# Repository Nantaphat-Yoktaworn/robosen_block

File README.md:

# Robosen Tangible Coding Block System & RobosenJS SDK

> **Physical Tangible Modular Coding Block System & Multi-Platform SDK for the Robosen K1 Humanoid Robot**  
> Designed for Screenless STEM Learning for Young Children ($\le 7$ Years Old) and Advanced Robotics Developers.  
> **FCC ID:** `2ATNWK1` | **Live Verified Robot ID:** `K1-00457` (`3C:A5:51:94:97:70`) | **Firmware:** `VER:3.03L`

---

## 📑 Table of Contents

1. [Executive Overview & Educational Mission](#-executive-overview--educational-mission)
2. [System Architecture & Signal Flow](#-system-architecture--signal-flow)
3. [2-Phase Bi-Directional Bus Protocol (CRC-8)](#-2-phase-bi-directional-bus-protocol-crc-8)
4. [Python Native BLE Subsystem & Daemon](#-python-native-ble-subsystem--daemon)
5. [Hardware & Electrical Specifications](#-hardware--electrical-specifications)
6. [Project Documentation Sitemap](#-project-documentation-sitemap)
7. [Developer Guide & Upstream RobosenJS SDK](#-developer-guide--upstream-robosenjs-sdk)

---

## 🎯 Executive Overview & Educational Mission

### The Core Problem
Most modern coding curricula for children rely on tablets, smartphones, or computers (e.g., Scratch, Blockly). However, for **young children aged 7 and under** (Piaget’s Preoperational and early Concrete Operational stages), screens present significant developmental hurdles:
- **Abstract vs. Concrete Cognition:** Young children learn best through tactile, physical manipulation rather than abstract 2D screen coordinates.
- **Screen Fatigue & Distraction:** Excessive screen time causes disengagement, eye strain, and cognitive overload.
- **Disconnected Output:** Virtual sprites on screens lack the visceral spatial feedback and excitement of watching a physical bipedal robot walk, punch, balance, and cheer.

### The Tangible Coding Solution
This project creates a **tangible, screenless, modular physical block programming system**. Children configure solid coding blocks on the Master's **Config Dock**, then snap them together in a line to create an algorithmic sequence at the **Run Port**. When they press the big **Green "Start" Button** on the Master Block, the sequence compiles instantly, verifies checksums, commands the **Robosen K1 humanoid robot** via Bluetooth Low Energy (BLE), and lights up each physical block with a **bright pulsating green LED** in real time as the robot executes each step!

```text
┌──────────────────────────────────────────────────────────────────────────────────────────────────┐
│                                   PHYSICAL TANGIBLE CODING CHAIN                                 │
│                                                                                                  │
│   [ MASTER BLOCK ] ──► [ WALK BLOCK ] ──► [ TURN BLOCK ] ──► [ PUNCH BLOCK ] ──► [ END BLOCK ]   │
│   (Brain, Battery,     (Param: 3 steps)   (Param: 90° Right) (Action: Left Hook) (Terminator)    │
│    E-Ink Display,                                                                                │
│    2 Config Knobs,                                                                               │
│    Start Button)                                                                                 │
│          │                                                                                       │
│          ▼ (Bluetooth BLE 4.2 / 5.0 Stream)                                                      │
│   [ ROBOSEN K1 HUMANOID ROBOT ] ─── Executes commands step-by-step with real-time feedback!      │
└──────────────────────────────────────────────────────────────────────────────────────────────────┘
```

---

## ⚡ System Architecture & Signal Flow

### 1. Dual-Mode Hardware Bus & Port Architecture

### 2. Config Mode: Flash Programming & Data Flow

### 3. Run Mode: End-to-End Execution & Protocol Data Flow

The system operates across three interconnected layers:
1. **Physical Modular Block Bus (4-Pin Magnetic Interface):** Master Block (ESP32-S3 with E-Ink & Config Dock) $\longleftrightarrow$ Solid Smart Blocks (WCH CH32V003 RISC-V) $\longleftrightarrow$ Smart End Block.
2. **Master Embedded & Control Gateway:** Master ESP32-S3 coordinates discovery frames (`0xAA`), CRC-8 validation, step broadcasts (`0xBB`), and non-blocking BLE command dispatch.
3. **Hardware Gateway & Robot Layer (Python BLE Daemon & Robosen K1):** Persistent BLE connection to Robosen K1 with dynamic 100% action completion ACK resolution.

```mermaid
sequenceDiagram
    autonumber
    participant Master as Master Block (ESP32-S3)
    participant Docked as Action Block (At Config Dock)
    participant B1 as Smart Block 1 (Walk 3 Steps)
    participant B2 as Smart Block 2 (Punch Left)
    participant EndBlock as Smart End Terminator
    participant Robot as Robosen K1 Humanoid Robot

    Note over Master,Docked: CONFIGURATION MODE (At Master Config Dock)
    Master->>Docked: Send Write Config [0xCF, 0x02, ActionID, Param, CRC, 0x55]
    Note over Docked: Saves [ActionID, Param] to Internal Flash Memory
    Docked-->>Master: Send ACK [0xCF, 0x06, CRC, 0x55]
    Note over Master,Docked: Block LED Pulses Emerald Green (Saved!)

    Note over Master,EndBlock: PHASE 1: DISCOVERY & COMPILATION (Press Start Button)
    Master->>B1: Frame [0xAA, Len=0, Count=0, CRC] (Pin 3 TX)
    Note over B1: Sets Index=1, appends Flash Token 0x01 (Walk) + Param=3, Count=1
    B1->>B2: Frame [0xAA, Len=2, Count=1, 0x01, 0x03, CRC]
    Note over B2: Sets Index=2, appends Flash Token 0x10 (Punch) + Param=1, Count=2
    B2->>EndBlock: Frame [0xAA, Len=4, Count=2, 0x01, 0x03, 0x10, 0x01, CRC]
    EndBlock->>Master: Return Verified Program Frame over Pin 4 (Return RX Rail)
    Master->>Master: Validates CRC-8 Checksum & Queues Sequence

    Note over Master,Robot: PHASE 2: REAL-TIME EXECUTION & VISUAL STEP TRACKING
    Master-->>B1: Broadcast [0xBB, ActiveStep=1, TotalSteps=2, CRC] (Pin 4 RX_BUS)
    Note over B1: MyIndex(1) == ActiveStep(1) -> GLOWS BRIGHT PULSING GREEN!
    Master->>Robot: Send BLE Walk Command (Opcode 0x01)
    Robot->>Master: Locomotion completes -> Master sends Stop (0x0C)
    
    Master-->>B2: Broadcast [0xBB, ActiveStep=2, TotalSteps=2, CRC] (Pin 4 RX_BUS)
    Note over B1: Reverts to Mode Color (Blue)
    Note over B2: MyIndex(2) == ActiveStep(2) -> GLOWS BRIGHT PULSING GREEN!
    Master->>Robot: Send BLE Action "ProAction/Left Punch" (Opcode 0x17)
    Robot->>Master: Robot streams progress -> reaches 100% ACK (0x64)

    Note over Master,Robot: SEQUENCE EXECUTION COMPLETED
    Master->>Master: E-Ink Display: 'MISSION COMPLETE 🎉'
    Robot->>Robot: Stabilizes into Safe Stand Posture & Idles
```

---

## 📡 2-Phase Bi-Directional Bus Protocol (CRC-8)

To achieve native physical order auto-discovery, hot-plug resilience, and real-time visual feedback over a simple 4-pin magnetic connector, the system uses an **Enhanced 2-Phase Bi-Directional UART Protocol**:

### Standardized 4-Pin Pogo Connector Pinout
* **Pin 1 (`V+`):** Regulated 3.3V power rail supplied by Master Block.
* **Pin 2 (`GND`):** Common system ground.
* **Pin 3 (`UART TX_DOWN`):** Downstream point-to-point serial line (Master $\to$ Block 1 $\to$ Block 2 $\dots \to$ End).
* **Pin 4 (`UART RX_BUS`):** Continuous return rail & real-time step broadcast bus.

### Binary Frame Structures
All serial transmissions use binary frames protected by **CRC-8** (Polynomial: $x^8 + x^2 + x + 1$, `0x07`):

1. **Phase 1: Discovery & Compilation Frame (`Header = 0xAA`)**
   ```
   [ 0xAA ] [ PacketLen (N) ] [ BlockCount (K) ] [ Block 1 ID ] [ Param 1 ] ... [ CRC-8 ] [ 0x55 ]
   ```
2. **Phase 2: Live Step Broadcast Frame (`Header = 0xBB`)**
   ```
   [ 0xBB ] [ ActiveStep (1-N / 0xFF) ] [ TotalSteps (N) ] [ CRC-8 ] [ 0x55 ]
   ```

### Command Token Catalog & LED Color Mapping

| Token ID | Command Name | Parameter | Robosen BLE Mapping | LED Color |
| :---: | :--- | :--- | :--- | :---: |
| `0x01` | `MOVE_FORWARD` | Steps (`1`–`5`) | `0x01` (Walk Forward) | 🔵 Blue (`#1E88E5`) |
| `0x02` | `MOVE_BACKWARD`| Steps (`1`–`5`) | `0x05` (Walk Backward) | 🔵 Dark Blue (`#1565C0`) |
| `0x03` | `TURN_LEFT` | Angle (`45°`–`180°`) | `0x08` (Turn Left) | 🔷 Cyan (`#00ACC1`) |
| `0x04` | `TURN_RIGHT` | Angle (`45°`–`180°`) | `0x02` (Turn Right) | 🔷 Cyan (`#00ACC1`) |
| `0x07` | `MOVE_LEFT` | Side-steps (`1`–`5`)| `0x07` (Step Left) | 🟦 Sky Blue (`#039BE5`) |
| `0x08` | `MOVE_RIGHT` | Side-steps (`1`–`5`)| `0x03` (Step Right) | 🟦 Sky Blue (`#039BE5`) |
| `0x10` | `LEFT_PUNCH` | Reps (`1`–`3`) | `0x17` (`"ProAction/Left Punch"`) | 🔴 Red (`#E53935`) |
| `0x11` | `RIGHT_PUNCH`| Reps (`1`–`3`) | `0x17` (`"ProAction/Right Punch"`) | 🔴 Bright Red (`#D32F2F`) |
| `0x12` | `KUNG_FU` | Reps (`1`–`3`) | `0x17` (`"ProAction/Kung Fu"`) | 🟠 Orange (`#FB8C00`) |
| `0x13` | `BOOGALOO` | Reps (`1`–`3`) | `0x17` (`"Action/Boogaloo"`) | 🟣 Magenta (`#8E24AA`) |
| `0x14` | `PUSH_UPS` | Reps (`1`–`3`) | `0x17` (`"ProAction/Push Ups"`) | 🟤 Brown (`#6D4C41`) |
| `0x15` | `HANDSTAND` | Reps (`1`–`3`) | `0x17` (`"ProAction/Handstand"`) | 🟤 Brown (`#6D4C41`) |
| `0x16` | `SINGLE_KICK`| Reps (`1`–`3`) | `0x17` (`"ProAction/Left Kick"`) | 🔴 Red (`#E53935`) |
| `0x17` | `DO_SQUATS` | Reps (`1`–`3`) | `0x17` (`"ProAction/Do Squats"`) | 🟢 Green (`#43A047`) |
| `0x18` | `SAY_HELLO` | Reps (`1`–`3`) | `0x17` (`"ProAction/Say Hello"`) | 🩵 Teal (`#00897B`) |
| `0x19` | `CELEBRATE` | Reps (`1`–`3`) | `0x17` (`"ProAction/Celebrate"`) | 🟡 Yellow (`#FDD835`) |
| `0xEE` | `END_CAP` | Smart End Terminator | N/A (Return Rail Loopback) | 🟢 Soft Emerald Green (`#00E020`) |

---

## 🐍 Python Native BLE Subsystem & Daemon

To provide 100% reliable Bluetooth Low Energy communication on Windows 11/10 without requiring C++ MSVC compiler toolchains, the project includes a native Python BLE subsystem powered by `bleak` and Windows WinRT:

### 1. Persistent BLE Daemon ([`scripts/k1_ble_daemon.py`](scripts/k1_ble_daemon.py))
- **Persistent Long-Lived Connection:** Connects once on startup and keeps the BLE connection alive to eliminate reconnection latency.
- **Dynamic 100% Action Completion ACK:** Listens to BLE Characteristic `0xFFE1` notifications in real time. Actions resolve the exact millisecond the physical robot emits `action_progress: 100%` (`0x64`), allowing seamless back-to-back chaining without hardcoded delays.
- **Standing Posture Preservation (`move_head_only`):** Captures live standing angles of all 16 body/leg servos via `0xE9` (`jointSync`) so neck/head articulations rotate smoothly without snapping leg angles or causing balance loss.
- **Bidirectional JSON IPC:** Communicates over `stdin`/`stdout` with CLI tools and background processes.

### 2. Fast Command-Line Execution CLI ([`scripts/k1_action.py`](scripts/k1_action.py))
```powershell
# Query Live Telemetry & Battery
python scripts/k1_action.py status

# Locomotion Steps
python scripts/k1_action.py walk
python scripts/k1_action.py turn_left
python scripts/k1_action.py turn_right

# Martial Arts & Combat
python scripts/k1_action.py punch_left
python scripts/k1_action.py punch_right
python scripts/k1_action.py kung_fu
python scripts/k1_action.py single_kick

# Stunts, Acrobatics & Dances
python scripts/k1_action.py push_ups
python scripts/k1_action.py handstand
python scripts/k1_action.py boogaloo
python scripts/k1_action.py say_hello
python scripts/k1_action.py celebrate
python scripts/k1_action.py do_squats

# Head Servo Articulations & Posture
python scripts/k1_action.py default_stand
python scripts/k1_action.py head_left
python scripts/k1_action.py head_right
python scripts/k1_action.py head_center
python scripts/k1_action.py head_pan
```

### 3. Interactive Joint Kinematics Controller ([`scripts/k1_joint_controller.py`](scripts/k1_joint_controller.py))
Interactive keyboard controller for all 17 digital servos with real-time safeguard limit enforcement, visual gauges, and error handling:
```powershell
python scripts/k1_joint_controller.py
```
- **Connection:** `C` (Connect/Reconnect) / `D` (Disconnect cleanly)
- **Select Joint:** `↑` / `↓` or `[` / `]` or Number `0`–`9`
- **Adjust Value:** `←` / `→` (or `PageDown` / `PageUp` for ±10)
- **Step Size:** `+` / `-` (1, 2, 5, 10)
- **Reset:** `R` (active joint) / `Shift+R` (all 17 stand pose)
- **Torque:** `U` (free joints for manual posing) / `L` (lock holding torque)

### 4. Interactive Telemetry & Control Suite ([`scripts/k1_ble_tester.py`](scripts/k1_ble_tester.py))
```powershell
python scripts/k1_ble_tester.py
```

---

## 🛠️ Hardware & Electrical Specifications

Complete hardware specifications are detailed in [`docs/specs/PHYSICAL_BLOCK_SYSTEM_SPEC.md`](file:///Users/nnnn/Projects/robosen_block/docs/specs/PHYSICAL_BLOCK_SYSTEM_SPEC.md), [`docs/specs/PROTOTYPE_00_SPEC.md`](file:///Users/nnnn/Projects/robosen_block/docs/specs/PROTOTYPE_00_SPEC.md) (Breadboard Proof-of-Concept), and [`docs/specs/PROTOTYPE_01_SPEC.md`](file:///Users/nnnn/Projects/robosen_block/docs/specs/PROTOTYPE_01_SPEC.md) (First Custom PCB Version):

### 1. Master Controller Breadboard Wiring & Pinout (Prototype #0)

```text
  (+) Red Rail  (+3.3V) ◄═════════[ 🔴 RED ]════════ ESP32 3V3 Pin
  (-) Blue Rail (GND)   ◄═════════[ ⚫ BLACK ]══════ ESP32 GND Pin

  [ KNOB 1: KY-040 Action Selector ]
   • VCC / +  ──► [ 🔴 RED ]    ──► (+) 3.3V Power Rail
   • GND      ──► [ ⚫ BLACK ]  ──► (-) Ground Rail
   • CLK      ──► [ 🟡 YELLOW ] ──► ESP32 GPIO 8
   • DT       ──► [ 🟢 GREEN ]  ──► ESP32 GPIO 9
   • SW       ──► [ 🔵 BLUE ]   ──► ESP32 GPIO 10

  [ KNOB 2: KY-040 Parameter Adjuster ]
   • VCC / +  ──► [ 🔴 RED ]    ──► (+) 3.3V Power Rail
   • GND      ──► [ ⚫ BLACK ]  ──► (-) Ground Rail
   • CLK      ──► [ ⚪ WHITE ]  ──► ESP32 GPIO 11 (CW = Increase)
   • DT       ──► [ 🟤 BROWN ]  ──► ESP32 GPIO 12
   • SW       ──► [ 🔘 GRAY ]   ──► ESP32 GPIO 13

  [ Tactile Start / Confirm Button - Green (4-Pin DIP, SW3) ]
   • Top-Right Pin ──► [ 🟠 ORANGE ] ──► ESP32 GPIO 14 (Internal Pull-Up)
   • Bottom-Left   ──► [ ⚫ BLACK ]  ──► (-) Ground Rail (Diagonal GND Return)

  [ Tactile Cancel / Stop Button - Red (4-Pin DIP, SW5) ]
   • Top-Right Pin ──► [ 🔴 RED/ORANGE ] ──► ESP32 GPIO 2 (Internal Pull-Up)
   • Bottom-Left   ──► [ ⚫ BLACK ]       ──► (-) Ground Rail (Diagonal GND Return)

  [ Battery Voltage Monitoring Divider (ADC1_CH0) ]
   • Divider Top   ──► VBAT_SW (Switched Battery Voltage Rail)
   • Midpoint (Sense)──► ESP32 GPIO 1 (BATSENSE) with 100nF Ceramic Filter Cap to GND
   • Divider Bottom──► (-) Ground Rail
```

| Component / Function | ESP32-S3 GPIO | Wire Color | Role / Description | Status |
| :--- | :---: | :---: | :--- | :---: |
| **+3.3V Power Rail** | `3V3` | 🔴 **Red** | Unified 3.3V DC Power Bus | ✅ Verified |
| **GND Common Rail** | `GND` | ⚫ **Black** | Common Ground Bus | ✅ Verified |
| **Battery Sense (ADC)** | `GPIO 1` | — | ADC1_CH0 1:1 Divider (100k/100k + 100nF) | ✅ Hardware Implemented |
| **Stop / Cancel Button**| `GPIO 2` | 🔴 **Red** | Red Tactile Button (`SW5`): Emergency Stop / Cancel / Back | ✅ Hardware Implemented |
| **Start / Run Button** | `GPIO 14` | 🟢/🟠 **Green/Orange**| Green Tactile Button (`SW3`): Confirm / Start / Next | ✅ Verified |
| **Knob 1 CLK** | `GPIO 8` | 🟡 **Yellow** | Action Selection Direction A | ✅ Verified |
| **Knob 1 DT** | `GPIO 9` | 🟢 **Green** | Action Selection Direction B | ✅ Verified |
| **Knob 1 SW** | `GPIO 10` | 🔵 **Blue** | Action Select Confirmation | ✅ Verified |
| **Knob 2 CLK** | `GPIO 11` | ⚪ **White** | Parameter Adjust Clock (CW = +) | ✅ Verified |
| **Knob 2 DT** | `GPIO 12` | 🟤 **Brown** | Parameter Adjust Data | ✅ Verified |
| **Knob 2 SW** | `GPIO 13` | 🔘 **Gray** | Parameter Reset / BLE Save | ✅ Verified |
| **Onboard Status RGB** | `GPIO 48` | *Internal* | 🟢 Ready \| 🔵 Scan \| 🟡 TX | ✅ Verified |
| **Config Dock UART** | `GPIO 17, 18` | 🔘 Gray / 🟣 Purple | Write Action (`0xCF`) & Read ACK | ✅ Verified |
| **Run Chain Bus UART**| `GPIO 15, 16` | 🟢 Green / ⚪ White | Phase 1 Discovery (`0xAA`) & Run (`0xBB`)| ✅ Verified |
| **E-Ink Display (SPI)** | `GPIO 4,5,6,7,21,38`| — | 2.13" DEPG0213BN SSD1680 (746ms Partial, Zero-Flicker Boot) | ✅ Verified |

### 2. Block Hardware Specifications
- **Master Block MCU:** ESP32-S3 (Dual-Core Xtensa LX7, Native Bluetooth BLE 5.0, SPI for E-Ink, and Dual UARTs for Config Dock & Run Chain).
- **Master UI & Display:** 2.13" E-Ink E-Paper display (DEPG0213BN / SSD1680, $71 \times 30\text{ mm}$ outline) + Dual Rotary Dials (Action & Parameter) + Dual Tactile Buttons (Green Start/Confirm & Red Stop/Cancel) + Battery Sense Monitor.
- **Visual Feedback (No Buzzer):** Master & Block WS2812B RGB LEDs with rich light choreography (emerald green flash ACK, data comet compilation wave, live step glowing green, rainbow victory sparkle).
- **Solid Modular Block MCUs (Unified Slave PCB):** Ultra-low-cost WCH CH32V003 (32-bit RISC-V, ~$0.15) with internal non-volatile flash parameter storage. **Action Blocks and Smart End Blocks share the exact same physical carrier PCB** ([`hardware/action_block/`](file:///Users/nnnn/Projects/robosen_block/hardware/action_block/)); End Block mode (`0xEE`) is configured via firmware on MCU Pin 15 (`PD0`), eliminating separate PCB fabrication or manual jumpers. Zero potentiometers or buttons on individual blocks!
- **Power & Charging:** Single 18650 3.7V Li-ion cell with onboard TP4056 USB-C charging, BMS protection, and TPS63020 3.3V synchronous buck-boost regulator.
- **Physical Connector:** Standardized 4-pin polarized magnetic pogo connector with reverse-polarity protection and RC debouncing filters.

### 3. Firmware Deliverables & Hardware Verification

| Module | Hardware Target | Source Location | Description | Status |
| :--- | :--- | :--- | :--- | :---: |
| **Master Controller** | ESP32-S3 | [`firmware/esp32_master/`](file:///Users/nnnn/Projects/robosen_block/firmware/esp32_master/) | BLE Central, NVS pairing, Dual-Knob UI, Dual Buttons (Green GPIO 14, Red GPIO 2), Battery ADC (GPIO 1), Run Chain Engine (`0xAA`/`0xBB`) | ✅ **Production Verified** |
| **Action Block Firmware** | WCH CH32V003 | [`firmware/ch32v003_action_block/`](file:///Users/nnnn/Projects/robosen_block/firmware/ch32v003_action_block/) | Unified C RISC-V firmware (2-Phase Binary V2, Config Dock, WS2812B) | ✅ **Flashed on Silicon** |
| **Smart End Block Firmware** | WCH CH32V003 | [`firmware/ch32v003_end_block/`](file:///Users/nnnn/Projects/robosen_block/firmware/ch32v003_end_block/) | Active loopback line driver, CRC-8 validation, rainbow sparkle (`0xEE`) | ✅ **Flashed on Silicon** |
| **Master Soldering Test** | ESP32-S3 | [`firmware/tests/master_soldering_test/`](file:///Users/nnnn/Projects/robosen_block/firmware/tests/master_soldering_test/) | All-input hardware verification suite (encoders, dual buttons, battery sense, e-paper, RGB) | ✅ **Hardware Verified** |
| **Standalone E-Ink Test** | ESP32-S3 | [`firmware/tests/standalone_eink_test/`](file:///Users/nnnn/Projects/robosen_block/firmware/tests/standalone_eink_test/) | 2.13" E-Paper DEPG0213BN driver benchmark, zero-flicker boot, partial refresh (1.34 Hz) | ✅ **Verified** |
| **ESP32 SWIO Programmer** | ESP32 / ESP32-S3 | [`firmware/tools_programmer/esp32_ch32v003_programmer/`](file:///Users/nnnn/Projects/robosen_block/firmware/tools_programmer/esp32_ch32v003_programmer/) | High-speed 1-wire SWIO debugger & chunked Python flasher (`flash_tool.py`) | ✅ **Utility** |
| **Arduino Uno Programmer** | Arduino Uno R3 | [`firmware/tools_programmer/arduino_uno_ch32v003_programmer/`](file:///Users/nnnn/Projects/robosen_block/firmware/tools_programmer/arduino_uno_ch32v003_programmer/) | Ardulink 16MHz assembly bit-banging flasher for `minichlink` | ✅ **Utility** |
| **Master Carrier PCB** | KiCad 10.0.6 | [`hardware/master_block/`](file:///Users/nnnn/Projects/robosen_block/hardware/master_block/) | Custom carrier motherboard PCB project (25.40mm row spacing, 100% routed, 0 DRC violations) | ✅ **Active Production Design** |
| **Modular Slave PCB (Action & End)** | KiCad 10.0.6 | [`hardware/action_block/`](file:///Users/nnnn/Projects/robosen_block/hardware/action_block/) | Unified 32×32mm carrier PCB for both Action Blocks and Smart End Blocks (Pin 15 / `PD0` configurable), centered pogo docks, 3-pin RGB header, 0 DRC violations | ✅ **Ordered & Verified** |

---

## 📚 Project Documentation Sitemap

| Document | Description |
| :--- | :--- |
| [`PROJECT_SUMMARY.md`](file:///Users/nnnn/Projects/robosen_block/PROJECT_SUMMARY.md) | Comprehensive executive project summary, mission, and comparison matrix |
| [`MEMORY.md`](file:///Users/nnnn/Projects/robosen_block/MEMORY.md) | Master technical knowledge base, verified hardware diagnostics, and opcode catalog |
| [`docs/specs/PHYSICAL_BLOCK_SYSTEM_SPEC.md`](file:///Users/nnnn/Projects/robosen_block/docs/specs/PHYSICAL_BLOCK_SYSTEM_SPEC.md) | Hardware, electrical, connector pinout, and 2-phase protocol specifications |
| [`docs/specs/PROTOTYPE_00_SPEC.md`](file:///Users/nnnn/Projects/robosen_block/docs/specs/PROTOTYPE_00_SPEC.md) | Prototype #0: Breadboard proof-of-concept engineering specification, wiring & test guides |
| [`docs/specs/PROTOTYPE_01_SPEC.md`](file:///Users/nnnn/Projects/robosen_block/docs/specs/PROTOTYPE_01_SPEC.md) | Prototype #1: First custom PCB release engineering specification, JLCPCB orders & assembly |
| [`docs/specs/PROTOTYPE_01_1_SPEC.md`](file:///Users/nnnn/Projects/robosen_block/docs/specs/PROTOTYPE_01_1_SPEC.md) | Prototype #1-1: Master Block PCB respin specification (ESP32-S3 25.40mm socket correction) |
| [`docs/specs/IMPROVEMENT_PLAN.md`](file:///Users/nnnn/Projects/robosen_block/docs/specs/IMPROVEMENT_PLAN.md) | 5-Pillar Master Improvement Plan and future production roadmap |
| [`docs/specs/ROBOSEN_K1_DOCUMENTATION.md`](file:///Users/nnnn/Projects/robosen_block/docs/specs/ROBOSEN_K1_DOCUMENTATION.md) | Official Robosen K1 reference manual, kinematics, voice commands, and safety guide |
| [`docs/master_block_wiring.html`](file:///Users/nnnn/Projects/robosen_block/docs/master_block_wiring.html) | Interactive Master Block BOM, color-coded pinout wiring table, and battery circuit guide |
| [`docs/mounting_and_enclosure_spec.md`](file:///Users/nnnn/Projects/robosen_block/docs/mounting_and_enclosure_spec.md) | Enclosure, M3 standoff boss clearances, and 3D casing specifications |
| [`docs/K1_HARDWARE_AUDIT_REPORT.md`](file:///Users/nnnn/Projects/robosen_block/docs/K1_HARDWARE_AUDIT_REPORT.md) | Live physical robot hardware diagnostics, telemetry verification, and action catalog dump |
| [`docs/plans/robosen_14_weeks_plan.md`](file:///Users/nnnn/Projects/robosen_block/docs/plans/robosen_14_weeks_plan.md) | 14-Week project operational timeline, task breakdown, and milestone tracking |
| [`docs/plans/TIMELINE_INFOGRAPHIC.md`](file:///Users/nnnn/Projects/robosen_block/docs/plans/TIMELINE_INFOGRAPHIC.md) | Timeline visual concept, ASCII art chart, and Canva design data |
| [`docs/assignments/RESEARCH_SUMMARY.md`](file:///Users/nnnn/Projects/robosen_block/docs/assignments/RESEARCH_SUMMARY.md) | Academic coursework research review summary (AS01) |
| [`hardware/master_block/`](file:///Users/nnnn/Projects/robosen_block/hardware/master_block/) | KiCad 10 Master Block PCB project (Corrected 25.40mm socket spacing, 100% routed) |
| [`hardware/action_block/`](file:///Users/nnnn/Projects/robosen_block/hardware/action_block/) | KiCad 10 Action Block PCB project, routing report, and production Gerbers |
| [`archive/prototype_1_0_retired/`](file:///Users/nnnn/Projects/robosen_block/archive/prototype_1_0_retired/) | Retired Prototype #1 files (preserved for historical defect audit) |

---

## 💻 Developer Guide & Upstream RobosenJS SDK

### Getting Started (Node.js SDK)
- Requires [Node.js](https://nodejs.org/en/download) (v22+)
- Install dependencies: `npm install`
- Run linting: `npm run lint`

### Programming API (JavaScript / TypeScript)
```js
import { K1 } from "robosen-js";

const k1 = new K1();
await k1.on();
await k1.volume(100);
await k1.autoStand(false);
await k1.moveForward();
await k1.leftPunch();
await k1.headLeft();
await k1.leftHand("+40%", 30);
await k1.audio("AppSysMS/101");
await k1.wait(3000);
await k1.end();
```

### CLI Utilities
```powershell
# Interactive REPL
npm run k1:repl

# Gamepad / Keyboard Controller
npm run k1:control

# Natural Language LLM Prompt (Requires OPENAI_API_KEY)
npm run k1:prompt
```

---

## 📄 License & Attribution

This project is licensed under the **[Apache License 2.0](LICENSE)**.

- **Original Base Library:** Core reverse-engineered protocol parser derived from [RobosenJS](https://github.com/oklemenz/RobosenJS) by Oliver Klemenz (Apache-2.0 License).
- **Physical Modular Tangible Coding Blocks:** Hardware specifications (CH32V003 bus, TP4056 power management) and 2-phase binary protocol with CRC-8 developed by [Nantaphat Yoktaworn](https://github.com/Nantaphat-Yoktaworn).
- **Python Subsystem:** Native background BLE daemon, IPC bridge, and interactive joint safeguard controller developed by [Nantaphat Yoktaworn](https://github.com/Nantaphat-Yoktaworn).
- **Trademarks:** Robosen is a registered trademark of Robosen Robotics. This open-source project is independently developed and not officially affiliated with or endorsed by Robosen.

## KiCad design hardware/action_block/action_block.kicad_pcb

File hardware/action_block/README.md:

# Robosen Tangible Action Block Hardware & PCB Design

> **Project:** Tangible Modular Coding Block System for Robosen Robot  
> **Target Module:** Modular Action Block (CH32V003 RISC-V Slave)  
> **Form Factor:** 32.0 mm × 32.0 mm 2-Layer FR-4 Carrier PCB (1.6 mm thickness, 1 oz copper)  
> **KiCad Version:** KiCad 10.0.6  
> **Fabrication Status:** **ORDERED AT JLCPCB (October 5, 2026)** — `robosen_action_block_gerbers.zip`  

---

## 1. System Overview & Electrical Architecture

Every Action Block is a drop-proof, solid modular unit with **zero moving parts** (no potentiometers, dials, or buttons). It contains:
1. **Microcontroller (`MCU`)**: **TENSTAR CH32V003F4P6** 2×11 DIP module (WCH 32-bit RISC-V core @ 24 MHz, 16 KB Flash, 2 KB SRAM).
2. **Visual Feedback (`RGB`)**: 3-pin 2.54 mm pitch header for a pre-soldered **WS2812 RGB LED module** (Top-to-Bottom: `GND`, `VCC`, `IN`).
3. **Decoupling Capacitor (`C104`)**: 100 nF ceramic capacitor placed adjacent to `VDD` and `GND`.
4. **Upstream Pogo Connector (`IN`)**: 4-pin 2.54 mm pitch magnetic pogo interface, **vertically centered** at $Y = 72.50\text{ mm}$.
5. **Downstream Pogo Connector (`OUT`)**: 4-pin 2.54 mm pitch magnetic pogo interface, **vertically centered** at $Y = 72.50\text{ mm}$ (ensures collinear flush alignment across chained blocks).
6. **Programming Header (`PROG`)**: 3-pin 2.54 mm header (`GND`, `3V3`, `SWIO`) for rapid 1-wire firmware flashing via `minichlink` or ESP32 programmer.

---

## 2. Pinout & Net Assignments

### 4-Pin Pogo Interface (`IN` & `OUT`, Centered at $Y = 72.50\text{ mm}$)

| Pin # | Signal Name | Upstream Connector (`IN`) | Downstream Connector (`OUT`) |
|:---:|:---|:---|:---|
| **1** | `+3V3` | Power Input ($Y = 68.69\text{ mm}$) | Power Output ($Y = 68.69\text{ mm}$) |
| **2** | `GND` | System Ground Reference ($Y = 71.23\text{ mm}$) | System Ground Reference ($Y = 71.23\text{ mm}$) |
| **3** | `UART_DATA` | Point-to-Point Input (`/RX_IN` $\to$ `PD6`, $Y = 73.77\text{ mm}$) | Point-to-Point Output (`/TX_OUT` $\gets$ `PD5`, $Y = 73.77\text{ mm}$) |
| **4** | `RETURN_BUS`| Continuous Return Rail Pass-Through ($Y = 76.31\text{ mm}$) | Continuous Return Rail Pass-Through ($Y = 76.31\text{ mm}$) |

> **Return Rail Detour:**  
> The `/RETURN_BUS` rail is routed on `B.Cu` ($0.40\text{ mm}$) with a 45° detour below the MCU DIP socket at $Y = 87.25\text{ mm}$ to prevent shorting through-hole pins 4 & 15.

### WS2812 RGB LED Header (`RGB`, 1×03 Pin Header)

| Pin # | Silk Label | Board Position ($X, Y$) | Net Assignment | Notes |
|:---:|:---|:---|:---|:---|
| **1** | `GND` | $(84.00, 59.96)\text{ mm}$ (Top) | `GND` | Thermal relief connection to continuous GND planes |
| **2** | `VCC` | $(84.00, 62.50)\text{ mm}$ (Middle) | `+3V3` | $0.60\text{ mm}$ power bus connection |
| **3** | `IN` | $(84.00, 65.04)\text{ mm}$ (Bottom) | `/LED_DIN` | High-speed 800 kHz signal to MCU pin 6 (`PA2`) |

### Programming & Debug Header (`PROG`, 1×03 Pin Header)

| Pin # | Silk Label | Board Position ($X, Y$) | Net Assignment |
|:---:|:---|:---|:---|
| **1** | `GND` | $(109.50, 81.42)\text{ mm}$ | `GND` |
| **2** | `3V3` | $(109.50, 83.96)\text{ mm}$ | `+3V3` |
| **3** | `SWIO` | $(109.50, 86.50)\text{ mm}$ | `/SWIO` (`PD1` on MCU pin 16) |

---

## 3. PCB Layout & Manufacturing Specifications

| Parameter | Specification |
| :--- | :--- |
| **Dimensions** | $32.00\text{ mm} \times 32.00\text{ mm}$ |
| **Layers** | 2 Layers (`F.Cu`, `B.Cu`) |
| **Thickness** | $1.6\text{ mm}$ FR-4 |
| **Copper Weight** | 1 oz ($35\text{ }\mu\text{m}$) |
| **Surface Finish** | Lead-Free HASL (or ENIG) |
| **Min Track / Spacing**| $0.30\text{ mm} / 0.25\text{ mm}$ ($0.60\text{ mm}$ for `+3V3`, $0.40\text{ mm}$ for `/RETURN_BUS`) |
| **Min Drill Size** | $0.85\text{ mm}$ (Zero vias; all connections use through-hole component pads) |
| **Ground Planes** | Continuous filled copper zones on both `F.Cu` and `B.Cu` with thermal reliefs |

---

## 4. Verification & Dual-Agent Audit

* **KiCad DRC**: **0 Errors, 0 Unconnected Items, 0 Copper Clearance Violations**.
* **Dual-Agent Verification**: Independently audited and verified by Antigravity and Codex Astra (`gpt-6-astra`).
* **Artifacts**:
  * Gerber Package: [`robosen_action_block_gerbers.zip`](robosen_action_block_gerbers.zip)
  * Schematic PDF: [`action_block_schematic.pdf`](action_block_schematic.pdf)
  * Top 3D Render: [`pcb_preview/action_block_top.png`](pcb_preview/action_block_top.png)
  * Bottom 3D Render: [`pcb_preview/action_block_bottom.png`](pcb_preview/action_block_bottom.png)
  * Routed Vector: [`pcb_preview/action_block_routed.svg`](pcb_preview/action_block_routed.svg)

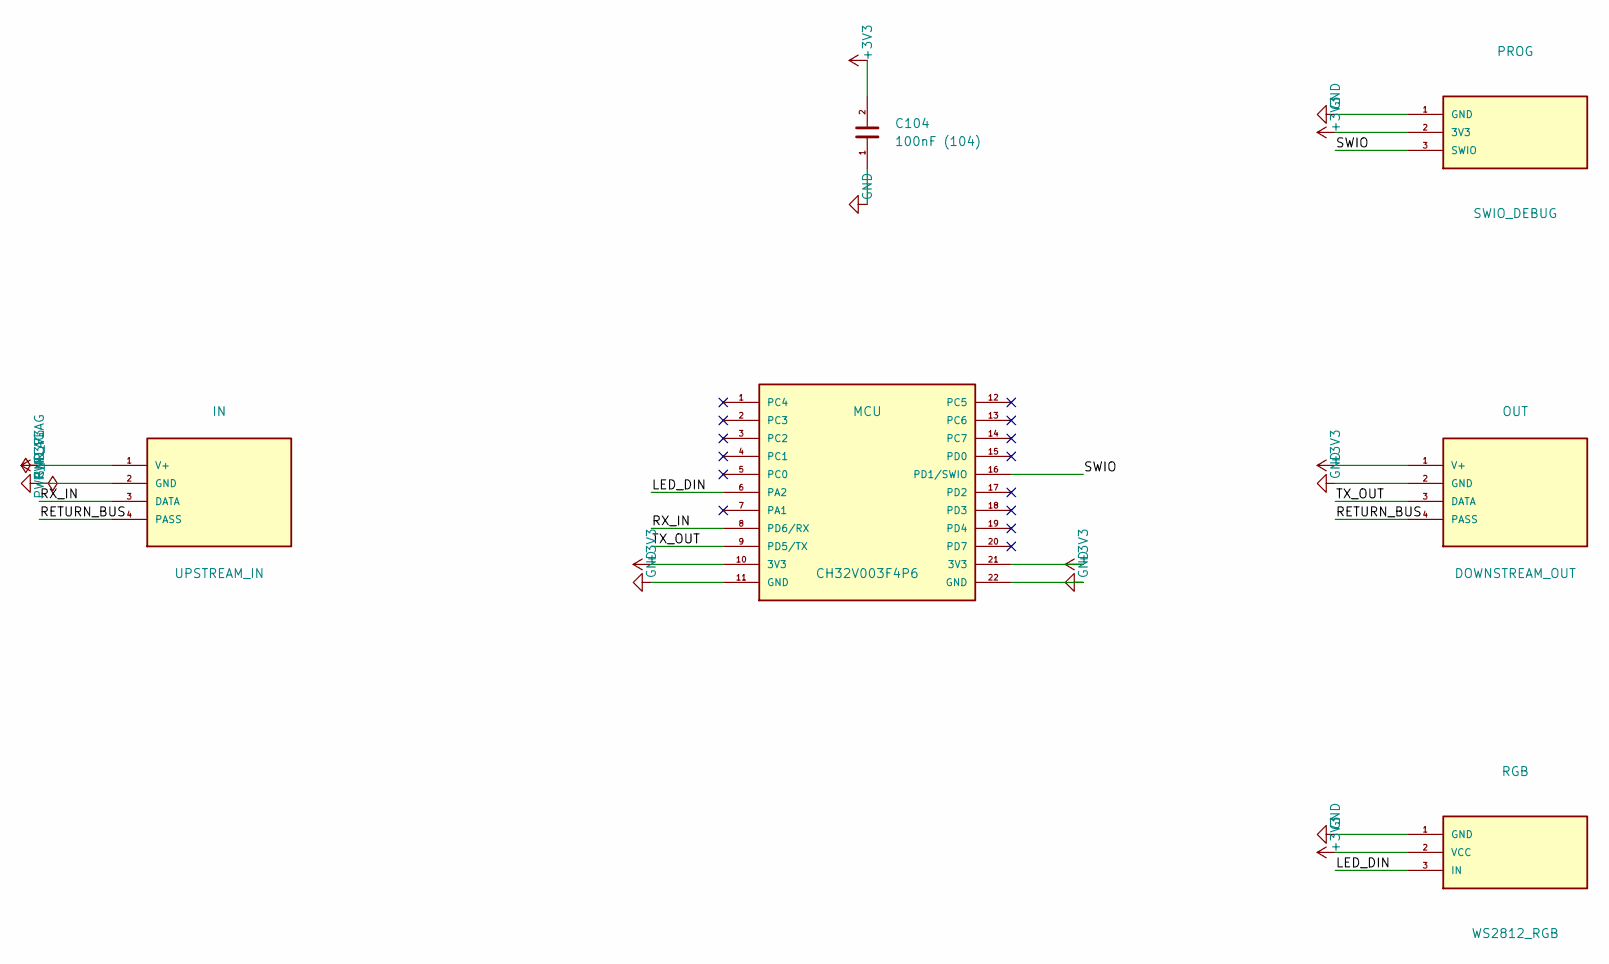
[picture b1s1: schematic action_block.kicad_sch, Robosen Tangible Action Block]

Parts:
C104: 100nF (104); C_Disc_P2.54mm
IN: UPSTREAM_IN; Pogo_4Pin_Dock_2.54mm
MCU: CH32V003F4P6; TENSTAR_CH32V003F4P6
OUT: DOWNSTREAM_OUT; Pogo_4Pin_Dock_2.54mm
PROG: SWIO_DEBUG; Prog_Header_1x03_P2.54mm
RGB: WS2812_RGB; WS2812B_Module_1x03_P2.54mm

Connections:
+3V3: C104.2, IN.1 (V+), MCU.10 (3V3), MCU.21 (3V3), OUT.1 (V+), PROG.2 (3V3), RGB.2 (VCC)
/LED_DIN: MCU.6 (PA2), RGB.3 (IN)
/RETURN_BUS: IN.4 (PASS), MCU.15 (PD0), OUT.4 (PASS)
/RX_IN: IN.3 (DATA), MCU.8 (PD6/RX)
/SWIO: MCU.16 (PD1/SWIO), PROG.3 (SWIO)
/TX_OUT: MCU.9 (PD5/TX), OUT.3 (DATA)
GND: C104.1, IN.2 (GND), MCU.11 (GND), MCU.22 (GND), OUT.2 (GND), PROG.1 (GND), RGB.1 (GND)

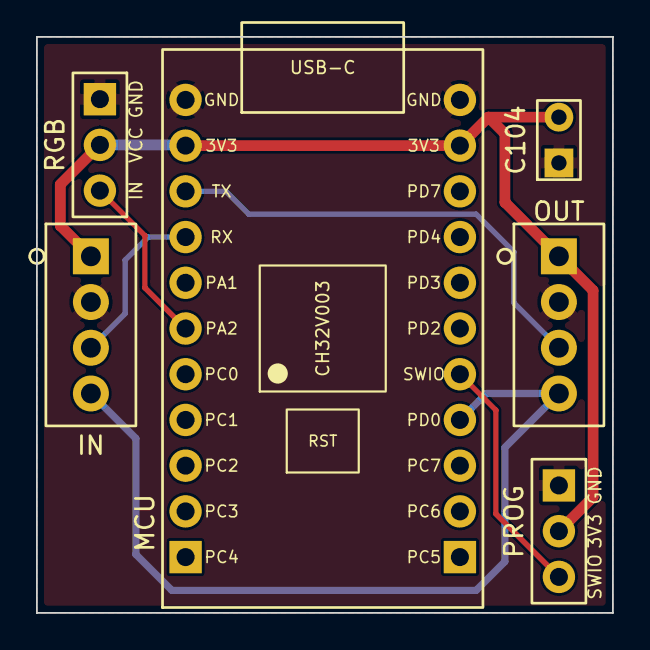
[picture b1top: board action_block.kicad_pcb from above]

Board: 2 copper layers, 32.0 x 32.0 mm, 6 parts (0 on the bottom side), 7 nets.

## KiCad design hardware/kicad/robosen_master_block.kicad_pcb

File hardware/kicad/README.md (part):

# Robosen K1 Master Block — KiCad 10 Hardware Project

> **Project:** Custom Carrier Motherboard PCB for Robosen K1 Tangible Coding Block  
> **KiCad Version:** KiCad 10.0.6 (Fully compatible with KiCad 8.x / 9.x / 10.x)  
> **Workspace Directory:** `hardware/kicad/`  
> **Schematic Status:** Fully pre-wired, verified with KiCad ERC (**0 violations**)  
> **PCB Routing Status:** 100% Routed, verified with KiCad DRC (**0 unconnected items**)  
> **Fabrication Files:** Gerbers & Excellon drill files generated and packaged in `robosen_master_block_gerbers.zip`  
> **Author:** Nantaphat Yoktaworn / Antigravity AI  

---

## 1. Project Directory Structure

```
hardware/kicad/
├── robosen_master_block.kicad_pro       # KiCad Master Project configuration
├── robosen_master_block.kicad_sch       # Complete pre-wired Starter Schematic (A3 format)
├── robosen_master_block.kicad_pcb       # Carrier Board PCB Layout (17 components pre-placed)
├── robosen_master_block.kicad_prl       # KiCad Project local settings
├── robosen_master_block.net             # Exported netlist (kicadsexpr format)
├── robosen_master_block_schematic.pdf   # High-resolution vector PDF export of schematic
├── footprint_svg/                       # Vector SVG renders of all 12 custom footprints
│   ├── 18650_Battery_Holder_Single.svg
│   ├── C_Disc_P2.54mm.svg
│   ├── EPaper_2.13in_Header_1x08.svg
│   ├── ESP32-S3-DevKitC-1-Socket.svg
│   ├── KY-040_Rotary_Encoder_Module.svg
│   ├── Pogo_4Pin_Dock_2.54mm.svg
│   ├── R_Axial_P10.16mm.svg
│   ├── SW_Power_2Wire_Pads.svg
│   ├── SW_PUSH_12x12mm.svg
│   ├── SW_Slide_SS12D00.svg
│   ├── TP4056_Type-C_Module.svg
│   └── TPS63020_BuckBoost_Module.svg
├── schematic_svg/
│   └── robosen_master_block.svg         # Vector SVG render of schematic
├── sym-lib-table                        # Project Symbol Library mapping table
├── robosen_master.kicad_sym             # Native KiCad symbol library (11 custom symbols)
├── fp-lib-table                         # Project Footprint Library mapping table
├── build_schematic.py                   # Automated Python generator for schematic & symlib
├── erc_report.txt                       # KiCad Electrical Rules Check report (0 violations)
├── TODO.md                              # Hardware & schematic design task checklist
├── README.md                            # Hardware documentation & pinout guide
└── robosen_master.pretty/               # Custom Footprint Library (12 verified .kicad_mod)
    ├── 18650_Battery_Holder_Single.kicad_mod# Keystone 1042 / BK-18650-PC2 Single-Cell Holder
    ├── C_Disc_P2.54mm.kicad_mod             # 100nF Ceramic Disc Capacitor for ADC filtering (2.54mm pitch)
    ├── EPaper_2.13in_Header_1x08.kicad_mod  # 8-Pin SPI header & 71x30mm mechanical outline (4x M2 holes)
    ├── ESP32-S3-DevKitC-1-Socket.kicad_mod   # Dual 22-pin header socket with 6x17.5mm antenna keepout
    ├── KY-040_Rotary_Encoder_Module.kicad_mod# 5-Pin Rotary Encoder Module breakout
    ├── Pogo_4Pin_Dock_2.54mm.kicad_mod      # Config Dock & Run Chain Bus Port
    ├── R_Axial_P10.16mm.kicad_mod           # 1/4W 10.16mm (0.4") Axial Resistors
    ├── SW_Power_2Wire_Pads.kicad_mod        # 2-Wire External Power Switch Solder Pads (1.2mm drill)
    ├── SW_PUSH_12x12mm.kicad_mod            # 12x12mm Tactile Push Button (START & STOP buttons)
    ├── SW_Slide_SS12D00.kicad_mod           # SS12D00 1P2T SPST Power Switch
    ├── TP4056_Type-C_Module.kicad_mod       # USB-C Lithium Charger + BMS Module
    └── TPS63020_BuckBoost_Module.kicad_mod  # 3.3V Synchronous Buck-Boost Regulator
```

---

## 2. Schematic Functional Architecture

The schematic is organized on an **A3 sheet** into 4 functional zones on a strict **1.27 mm (50 mil) grid**:

```
+-----------------------------------------------------------------------------------------+
|                                    A3 SCHEMATIC SHEET                                   |
|                                                                                         |
|  [ ZONE 1: USER INTERFACE ]               [ ZONE 2: CORE MCU ]                          |
|  - Knob 1: KY-040 Action (SW1)            - ESP32-S3 DevKitC-1 (U1)                     |
|  - Knob 2: KY-040 Param (SW2)               * SPI BUS -> EPD Display                    |
|  - Confirm / Start: 12mm Push [Green] (SW3) * UART1   -> Config Dock (J1)               |
|  - Cancel / Stop: 12mm Push [Red] (SW5)     * UART2   -> Run Chain Bus (J2)             |
|  - Display: 2.13" E-Paper Header (DISP1)    * GPIO 8-14, 2 -> Encoders & Dual Buttons   |
|                                             * GPIO 1 (ADC1_CH0) -> Battery Sense Divider|
|                                                                                         |
|                                           [ ZONE 3: DOCKS & BUS PULL-UPS ]              |
|                                           - Config Dock Port (J1)                       |
|                                           - Run Chain Port (J2)                         |
|                                           - R1 / R2: 10k Pull-ups for Open-Drain Chain  |
|                                                                                         |
|                                           [ ZONE 4: POWER & CHARGING ]                  |
|                                           - BT1 (18650 3.7V Li-ion Cell)                |
|                                           - U2 (TP4056 USB-C Charger & Protection)      |
|                                           - SW4 (SS12D00 SPST Power Switch)             |
|                                           - U3 (TPS63020 3.3V Synchronous Buck-Boost)   |
|                                           - R3/R4/C1 (100k Battery Sense Divider + ADC) |
+-----------------------------------------------------------------------------------------+
```

---

## 3. Pre-Wired Net Connections & Pinout Table

| Net Name | Origin Pin | Destination Pin | Description |
|:---|:---|:---|:---|
| **`K1_CLK`** | SW1 Pin 1 (`CLK`) | U1 Pin 12 (`GPIO8`) | Action Knob quadrature phase A |
| **`K1_DT`** | SW1 Pin 2 (`DT`) | U1 Pin 15 (`GPIO9`) | Action Knob quadrature phase B |
| **`K1_SW`** | SW1 Pin 3 (`SW`) | U1 Pin 16 (`GPIO10`) | Action Knob push button switch |
| **`K2_CLK`** | SW2 Pin 1 (`CLK`) | U1 Pin 17 (`GPIO11`) | Parameter Knob quadrature phase A |
| **`K2_DT`** | SW2 Pin 2 (`DT`) | U1 Pin 18 (`GPIO12`) | Parameter Knob quadrature phase B |
| **`K2_SW`** | SW2 Pin 3 (`SW`) | U1 Pin 19 (`GPIO13`) | Parameter Knob push button switch |
| **`BTN_START`**| SW3 Pin 1 (`1`) | U1 Pin 20 (`GPIO14`) | 12mm tactile Confirm / Start / Next button [Green] |
| **`BTN_STOP`** | SW5 Pin 1 (`1`) | U1 Pin 27 (`GPIO2`) | 12mm tactile Cancel / Stop / Back button [Red] |
| **`BATSENSE`** | R3:2, R4:1, C1:1 | U1 Pin 26 (`GPIO1`) | Battery voltage sense divider midpoint (1/2 Vbat) with 100nF filter |
| **`EPD_BUSY`** | DISP1 Pin 1 (`BUSY`) | U1 Pin 4 (`GPIO4`) | E-Paper busy status output |
| **`EPD_CS`** | DISP1 Pin 2 (`CS`) | U1 Pin 7 (`GPIO7`) | E-Paper SPI chip select |
| **`EPD_DC`** | DISP1 Pin 3 (`DC`) | U1 Pin 6 (`GPIO6`) | E-Paper data/command select |
| **`EPD_RES`** | DISP1 Pin 4 (`RES`) | U1 Pin 5 (`GPIO5`) | E-Paper hardware reset |
| **`EPD_MOSI`** | DISP1 Pin 5 (`SDA`) | U1 Pin 32 (`GPIO38`) | SPI MOSI data to display |
| **`EPD_SCK`** | DISP1 Pin 6 (`SCL`) | U1 Pin 40 (`GPIO21`) | SPI clock to display |
| **`CFG_TX`** | U1 Pin 10 (`GPIO17`) | J1 Pin 4 (`PASS`) | Config Dock UART TX output |
| **`CFG_RX`** | U1 Pin 11 (`GPIO18`) | J1 Pin 3 (`DATA`) | Config Dock UART RX input |
| **`CHAIN_TX`** | U1 Pin 8 (`GPIO15`) | J2 Pin 3 (`DATA`), R1 Pin 2 | Command TX to first instruction block |
| **`CHAIN_RX`** | U1 Pin 9 (`GPIO16`) | J2 Pin 4 (`PASS`), R2 Pin 2 | Status RX from last instruction block |
| **`VBAT_RAW`** | BT1 Pin 1 (`+`) | U2 Pin 2 (`B+`) | Raw battery positive terminal |
| **`VBAT_GND`** | BT1 Pin 2 (`-`) | U2 Pin 3 (`B-`) | Raw battery negative terminal |
| **`VBAT_PROT`**| U2 Pin 1 (`OUT+`) | SW4 Pin 1 (`1`) | Protected battery voltage to switch |
| **`VBAT_SW`** | SW4 Pin 2 (`2`) | U3 Pin 3, Pin 4 (`VIN`), R3:1 | Switched battery power into regulator and sense divider |
| **`+3V3`** | U3 Pin 7, Pin 8 (`OUT`) | U1:1, U1:2, SW1:4, SW2:4, DISP1:7, J1:1, J2:1, R1:1, R2:1 | Regulated system power rail |
| **`GND`** | System Common Rail | U1:22,23,43,44, SW1:5, SW2:5, SW3:2, SW5:2, DISP1:8, J1:2, J2:2, U2:4, U3:1,2,5,6, R4:2, C1:2 | System ground rail |

---

## 4. Verified Custom Footprints & Physical Measurements

All 12 custom footprints in `robosen_master.pretty/` have been created and verified against manufacturer mechanical drawings and physical caliper measurements:

### 1. ESP32-S3-DevKitC-1-Socket (`U1`)
- **Format:** Dual 22-pin female header sockets spaced **0.900" (22.86 mm)** row-to-row.
- **Orientation:** Antenna at **TOP**, Dual USB-C ports at **BOTTOM**.
- **Antenna Overhang & RF Keepout:** $17.5\text{ mm} \text{ wide} \times 6.0\text{ mm} \text{ stick-out}$ ($X \in [-8.75, +8.75]$, $Y \in [-35.0, -29.0]$) with a strict all-layer copper keepout zone (`keepout_copper`) under and around the RF antenna region.
- **Pin Numbering:**
  - Left Row: Pads **1 to 22** (Pin 1 `3V3` at top, Pin 22 `GND` at bottom).
  - Right Row: Pads **23 to 44** (Pin 23 `GND` at top, Pin 44 `IO21` at bottom).
  - Strictly aligned with Espressif official DevKitC-1 pinout and physical board silkscreen.

### 2. 2.13" E-Paper Display Module (`DISP1`)
- **Module Physical Boundary:** $71.0\text{ mm} \times 30.0\text{ mm}$ on `F.SilkS` and `F.Fab`.
- **Active Display Area:** $48.55\text{ mm} \times 23.71\text{ mm}$ (2.13" diagonal, $250 \times 122$ pixels) and $59.2\text{ mm} \times 29.2\text{ mm}$ glass outline drawn on `F.Fab`.
- **Mounting Holes:** 4× M2 NPTH holes (Ø $2.2\text{ mm}$) inset $2.5\text{ mm}$ from all four corners ($X = \pm 33.0\text{ mm}$, $Y = \pm 12.5\text{ mm}$).
- **Pin Header:** 1×08 $2.54\text{ mm}$ pitch vertical through-hole header centered on the left edge ($1.5\text{ mm}$ from left edge, $X = -34.0\text{ mm}$, $Y \in [-8.89, +8.89]$).
- **Pinout (Top to Bottom):** `1:BUSY`, `2:CS`, `3:DC`, `4:RES`, `5:SDA`, `6:SCL`, `7:VCC`, `8:GND`.

### 3. TPS63020 3.3V Synchronous Buck-Boost (`U3`)
- **Manufacturer Dimensions:** $26.32\text{ mm} \times 17.51\text{ mm}$ ($1036.19 \times 689.20\text{ mils}$).
- **Horizontal Pin Separation:** $23.78\text{ mm}$ center-to-center ($X = \pm 11.89\text{ mm}$).
- **Vertical Pin Pitch:** $2.54\text{ mm}$ (100 mil) standard header pitch within each corner pair.
- **Hole Diameter:** 1.0 mm drill, 1.8 mm annular ring.
- **Pinout:**
  - Left (IN): Pads 1 & 2 = `GND` (top), Pads 3 & 4 = `VIN` (bottom).
  - Right (OUT): Pads 5 & 6 = `GND` (top), Pads 7 & 8 = `OUT` / +3.3V (bottom).

### 4. TP4056 Type-C Charger & BMS Module (`U2`)
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
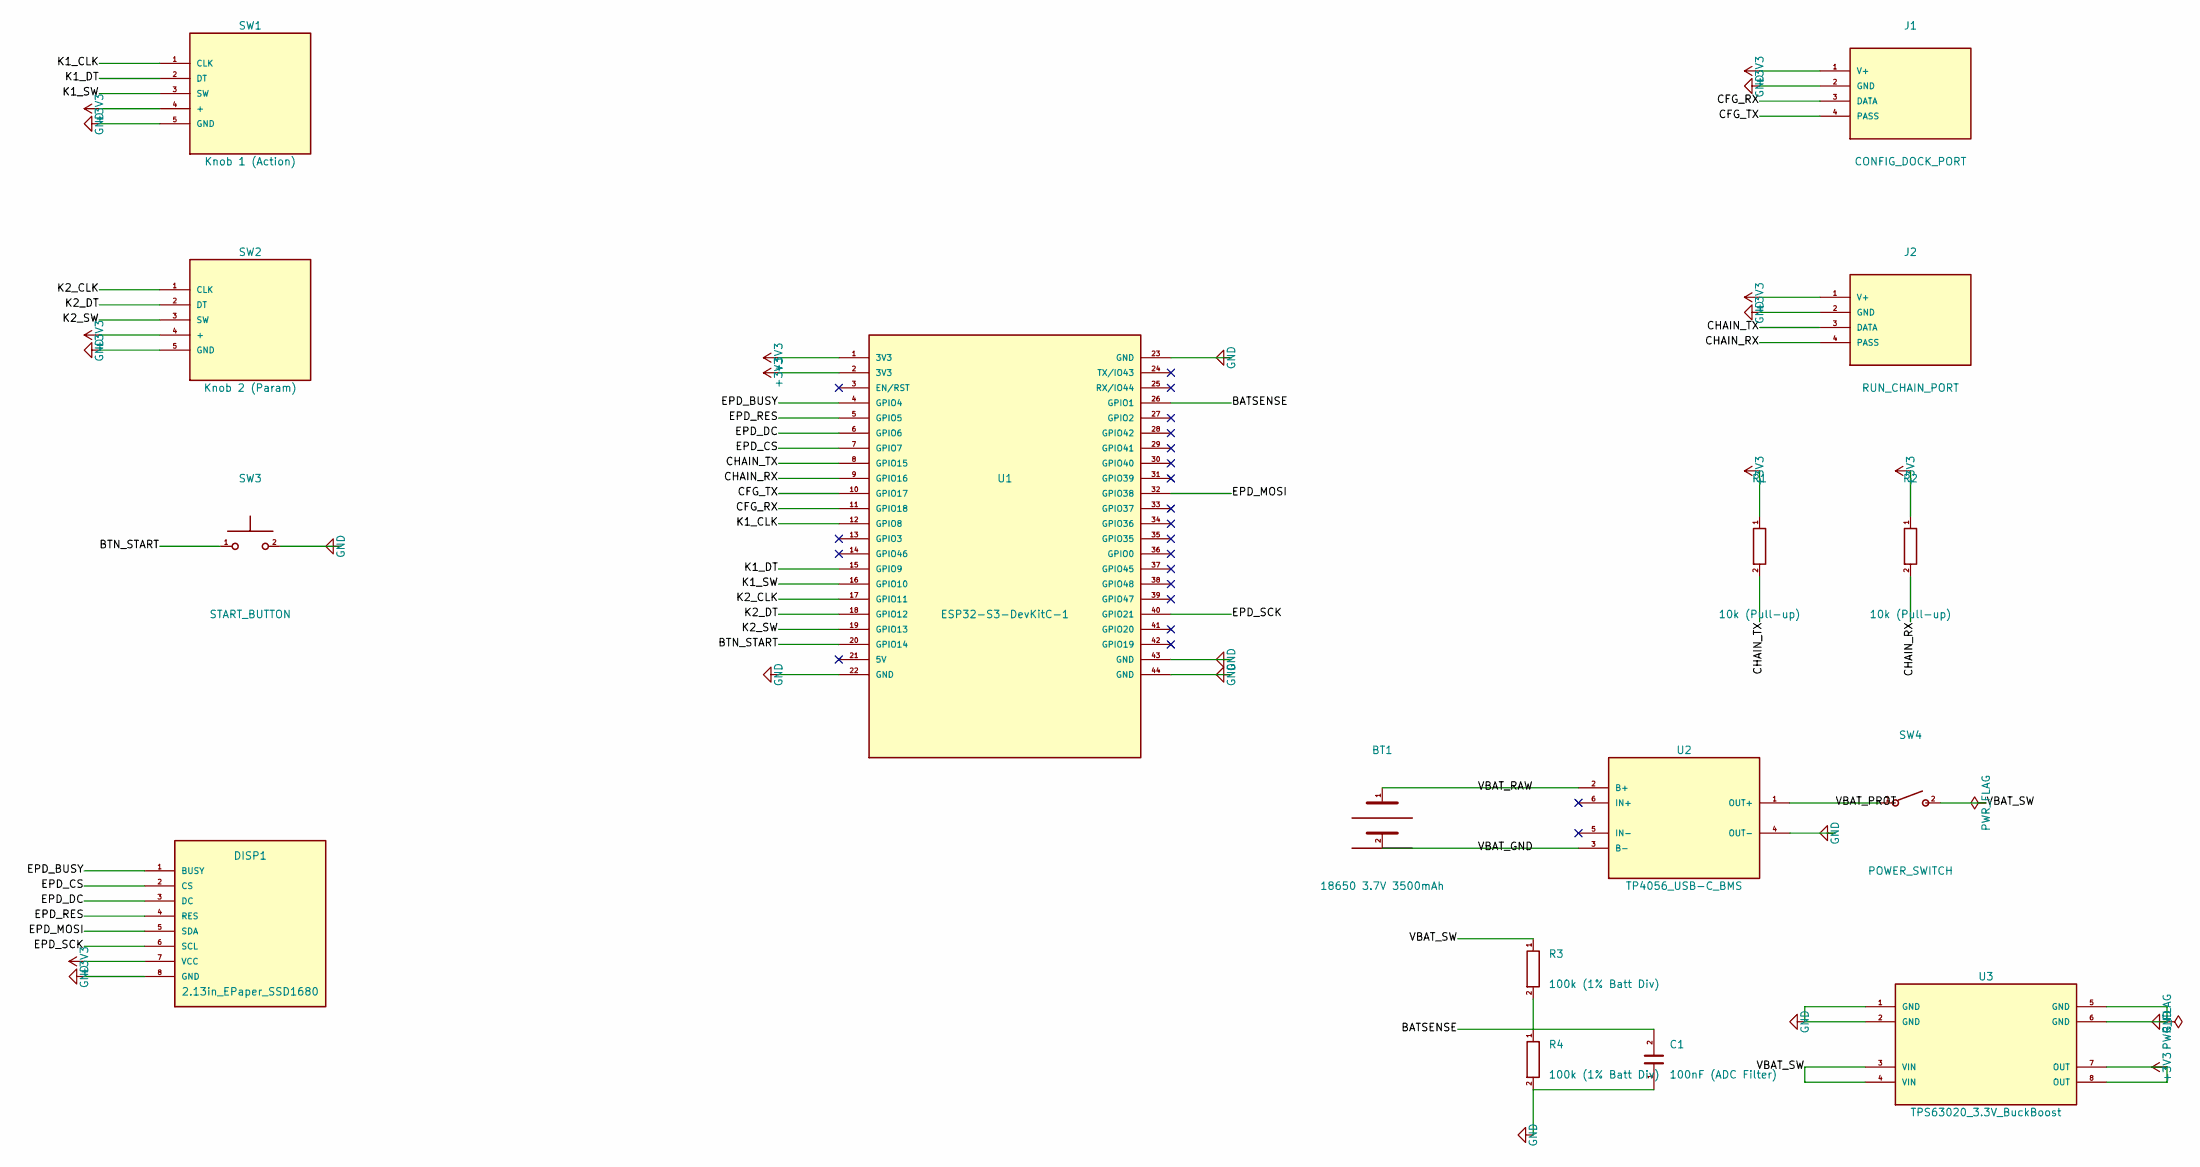
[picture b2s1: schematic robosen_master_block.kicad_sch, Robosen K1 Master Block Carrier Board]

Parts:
BT1: 18650 3.7V 3500mAh; 18650_Battery_Holder_Single
C1: 100nF (ADC Filter); C_Disc_P2.54mm
DISP1: 2.13in_EPaper_SSD1680; EPaper_2.13in_Header_1x08
J1: CONFIG_DOCK_PORT; Pogo_4Pin_Dock_2.54mm
J2: RUN_CHAIN_PORT; Pogo_4Pin_Dock_2.54mm
R1, R2: 10k (Pull-up); R_Axial_P10.16mm
R3, R4: 100k (1% Batt Div); R_Axial_P10.16mm
SW1: Knob 1 (Action); KY-040_Rotary_Encoder_Module
SW2: Knob 2 (Param); KY-040_Rotary_Encoder_Module
SW3: START_BUTTON; SW_PUSH_12x12mm
SW4: POWER_SWITCH; SW_Power_2Wire_Pads
U1: ESP32-S3-DevKitC-1; ESP32-S3-DevKitC-1-Socket
U2: TP4056_USB-C_BMS; TP4056_Type-C_Module
U3: TPS63020_3.3V_BuckBoost; TPS63020_BuckBoost_Module

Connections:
+3V3: DISP1.7 (VCC), J1.1 (V+), J2.1 (V+), R1.1, R2.1, SW1.4 (+), SW2.4 (+), U1.1 (3V3), U1.2 (3V3), U3.7 (OUT), U3.8 (OUT)
/BATSENSE: C1.2, R3.2, R4.1, U1.26 (GPIO1)
/BTN_START: SW3.1, U1.20 (GPIO14)
/BTN_STOP: U1.27 (GPIO2); also elsewhere on the board
/CFG_RX: J1.3 (DATA), U1.11 (GPIO18)
/CFG_TX: J1.4 (PASS), U1.10 (GPIO17)
/CHAIN_RX: J2.4 (PASS), R2.2, U1.9 (GPIO16)
/CHAIN_TX: J2.3 (DATA), R1.2, U1.8 (GPIO15)
/EPD_BUSY: DISP1.1 (BUSY), U1.4 (GPIO4)
/EPD_CS: DISP1.2 (CS), U1.7 (GPIO7)
/EPD_DC: DISP1.3 (DC), U1.6 (GPIO6)
/EPD_MOSI: DISP1.5 (SDA), U1.32 (GPIO38)
/EPD_RES: DISP1.4 (RES), U1.5 (GPIO5)
/EPD_SCK: DISP1.6 (SCL), U1.40 (GPIO21)
/K1_CLK: SW1.1 (CLK), U1.12 (GPIO8)
/K1_DT: SW1.2 (DT), U1.15 (GPIO9)
/K1_SW: SW1.3 (SW), U1.16 (GPIO10)
/K2_CLK: SW2.1 (CLK), U1.17 (GPIO11)
/K2_DT: SW2.2 (DT), U1.18 (GPIO12)
/K2_SW: SW2.3 (SW), U1.19 (GPIO13)
/VBAT_GND: BT1.2 (-), U2.3 (B-)
/VBAT_PROT: SW4.1, U2.1 (OUT+)
/VBAT_RAW: BT1.1 (+), U2.2 (B+)
/VBAT_SW: R3.1, SW4.2, U3.3 (VIN), U3.4 (VIN)
GND: C1.1, DISP1.8 (GND), J1.2 (GND), J2.2 (GND), R4.2, SW1.5 (GND), SW2.5 (GND), SW3.2, U1.22 (GND), U1.23 (GND), U1.43 (GND), U1.44 (GND), U2.4 (OUT-), U3.1 (GND), U3.2 (GND), U3.5 (GND), U3.6 (GND); also elsewhere on the board

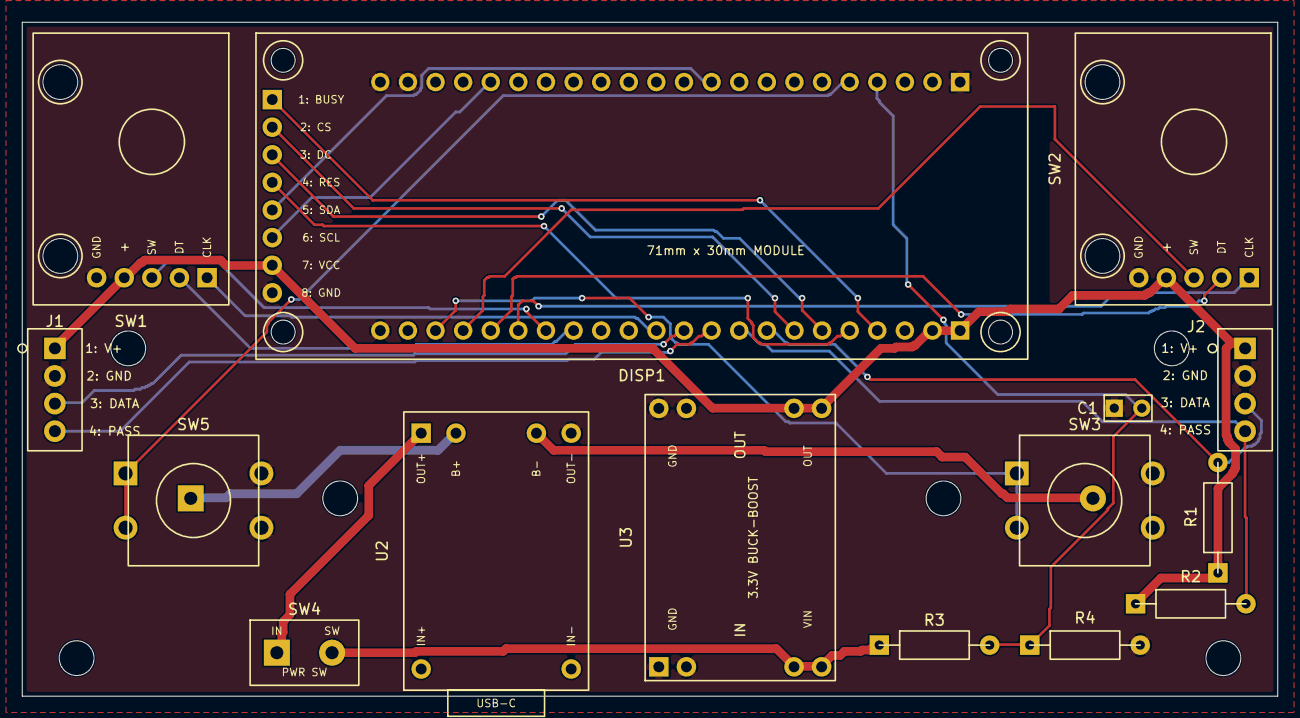
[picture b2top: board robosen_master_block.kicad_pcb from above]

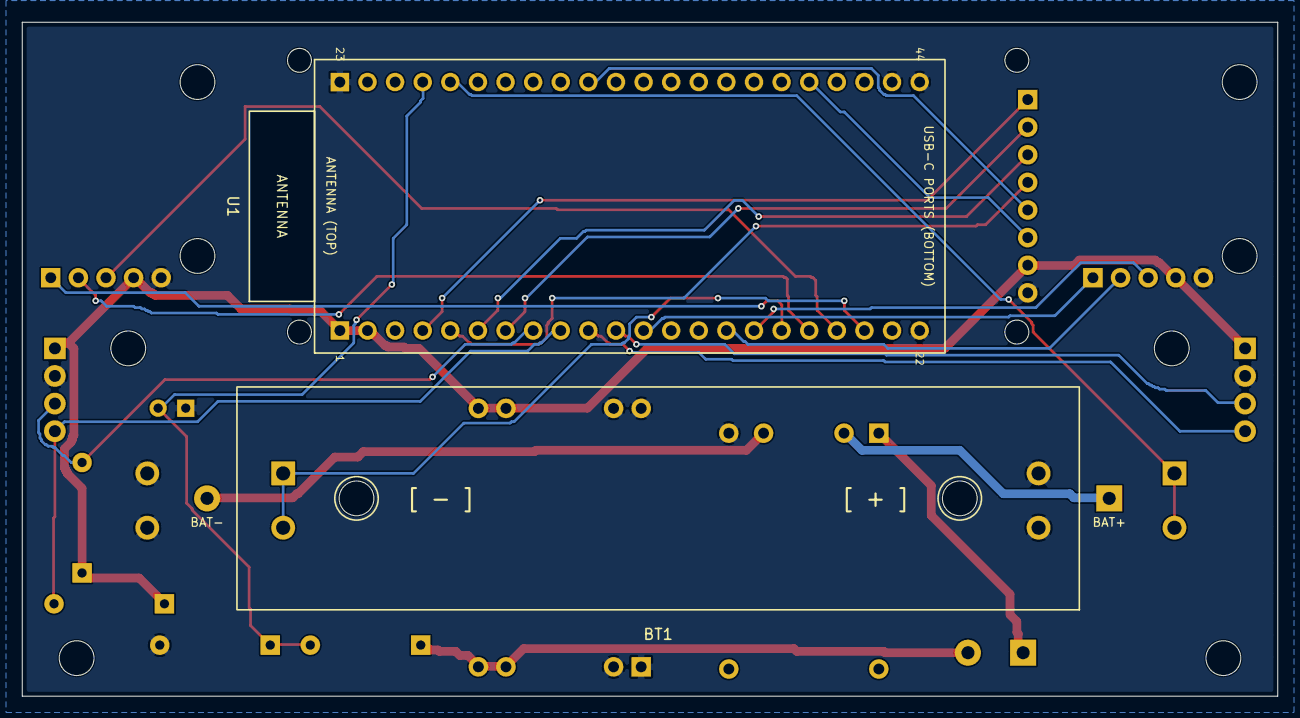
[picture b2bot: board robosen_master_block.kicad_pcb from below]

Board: 2 copper layers, 115.5 x 62.0 mm, 21 parts (2 on the bottom side), 25 nets.

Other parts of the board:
H1, H2, H3, H4: MountingHole_3.2mm_M3
SW5: CANCEL_STOP (Red); SW_PUSH_12x12mm

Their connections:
/BTN_STOP: SW5.1; also elsewhere on the board
GND: SW5.2; also elsewhere on the board
